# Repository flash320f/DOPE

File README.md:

# DOPE-PAD

It is dope for a reason. It is simple and extremely functional. The copy function and paste function is integrated to individual keys along with two slangs in other two keys.
It is a 4-key Macropad with a rotary encoder.

# Features

Microcontroller: Seeed XIAO RP 2040
Firmware: KMK
4-Keys + 2 little LEDs

# Here's the visuals of DOPE-Pad

|  |  |  |
| :---: | :---: | :---: |
| **Macropad** | **Top View** | **Base** |

|  |  |  |
| :---: | :---: | :---: |
| **Schematic** | **PCB Layout** | **Assembled Board** |

# BOM
Here is the file for BOM: [VIEW the BOM](bom.csv)

It is very Basic and simple. Desogn-wise and functionality-wise.

Thanks for reading!

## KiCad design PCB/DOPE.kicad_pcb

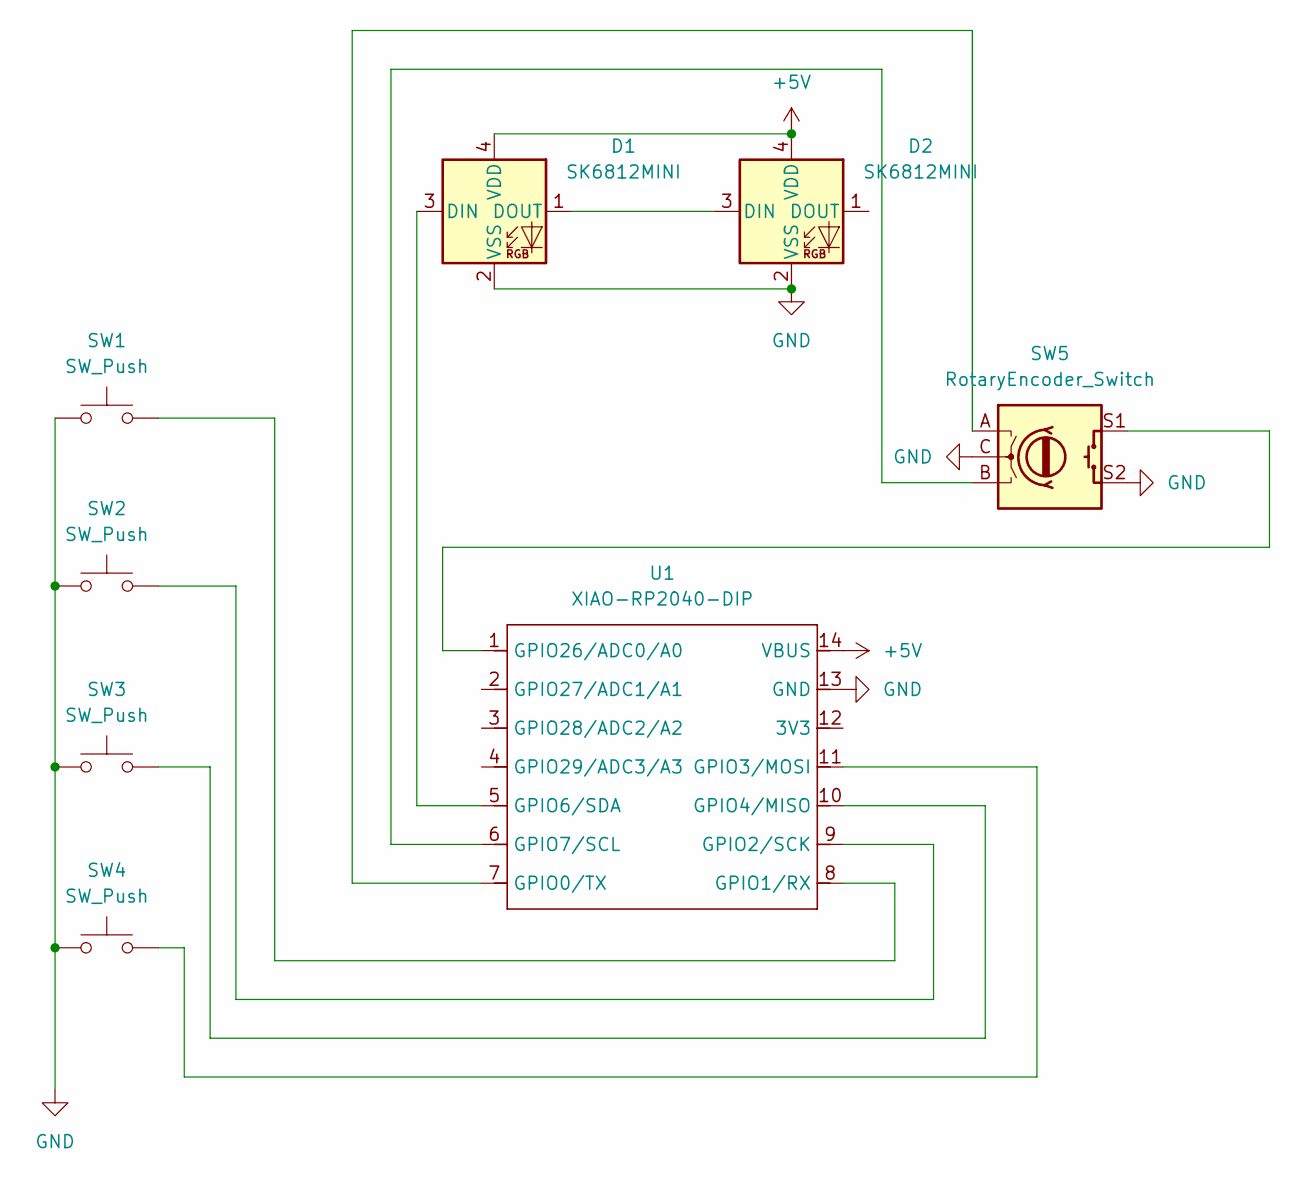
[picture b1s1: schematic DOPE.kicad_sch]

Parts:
D1, D2: SK6812MINI; LED_SK6812MINI_PLCC4_3.5x3.5mm_P1.75mm
SW1, SW2, SW3, SW4: SW_Push; SW_Cherry_MX_1.00u_PCB
SW5: RotaryEncoder_Switch; RotaryEncoder_Alps_EC11E-Switch_Vertical_H20mm
U1: XIAO-RP2040-DIP

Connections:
+5V: D1.4 (VDD), D2.4 (VDD), U1.14 (VBUS)
GND: D1.2 (VSS), D2.2 (VSS), SW1.1, SW2.1, SW3.1, SW4.1, SW5.C, SW5.S2, U1.13 (GND)
unnamed: D1.3 (DIN), U1.5 (GPIO6/SDA)
unnamed: D1.1 (DOUT), D2.3 (DIN)
unnamed: SW5.A, U1.7 (GPIO0/TX)
unnamed: SW1.2, U1.8 (GPIO1/RX)
unnamed: SW2.2, U1.9 (GPIO2/SCK)
unnamed: SW4.2, U1.11 (GPIO3/MOSI)
unnamed: SW3.2, U1.10 (GPIO4/MISO)
unnamed: SW5.B, U1.6 (GPIO7/SCL)
unnamed: SW5.S1, U1.1 (GPIO26/ADC0/A0)

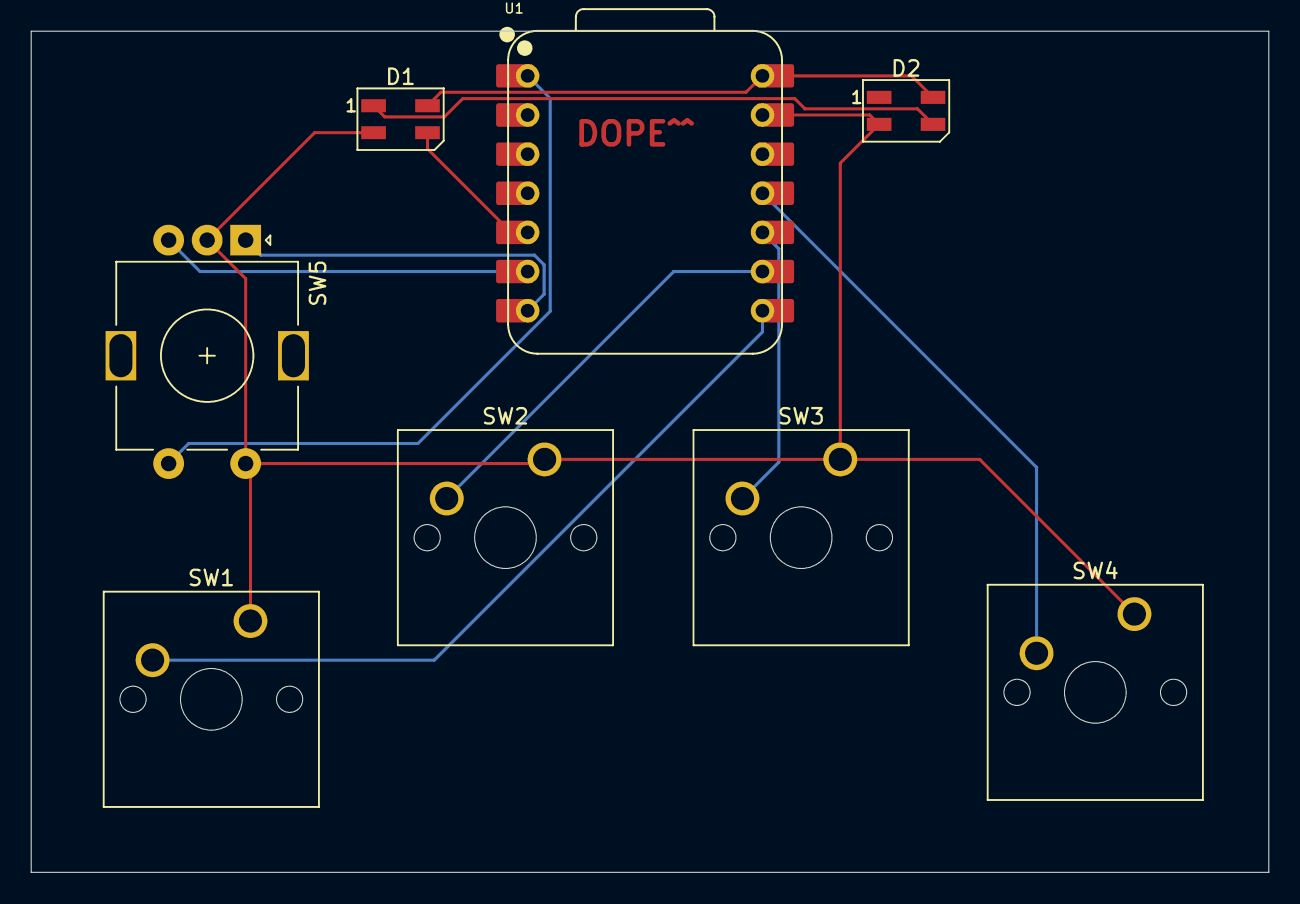
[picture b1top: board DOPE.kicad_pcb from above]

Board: 2 copper layers, 80.3 x 54.6 mm, 8 parts (0 on the bottom side), 11 nets.

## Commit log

2025-12-01 Add README
2025-12-02 Refining the structure
2025-12-02 Modified README
2025-12-03 BOM CSV added
